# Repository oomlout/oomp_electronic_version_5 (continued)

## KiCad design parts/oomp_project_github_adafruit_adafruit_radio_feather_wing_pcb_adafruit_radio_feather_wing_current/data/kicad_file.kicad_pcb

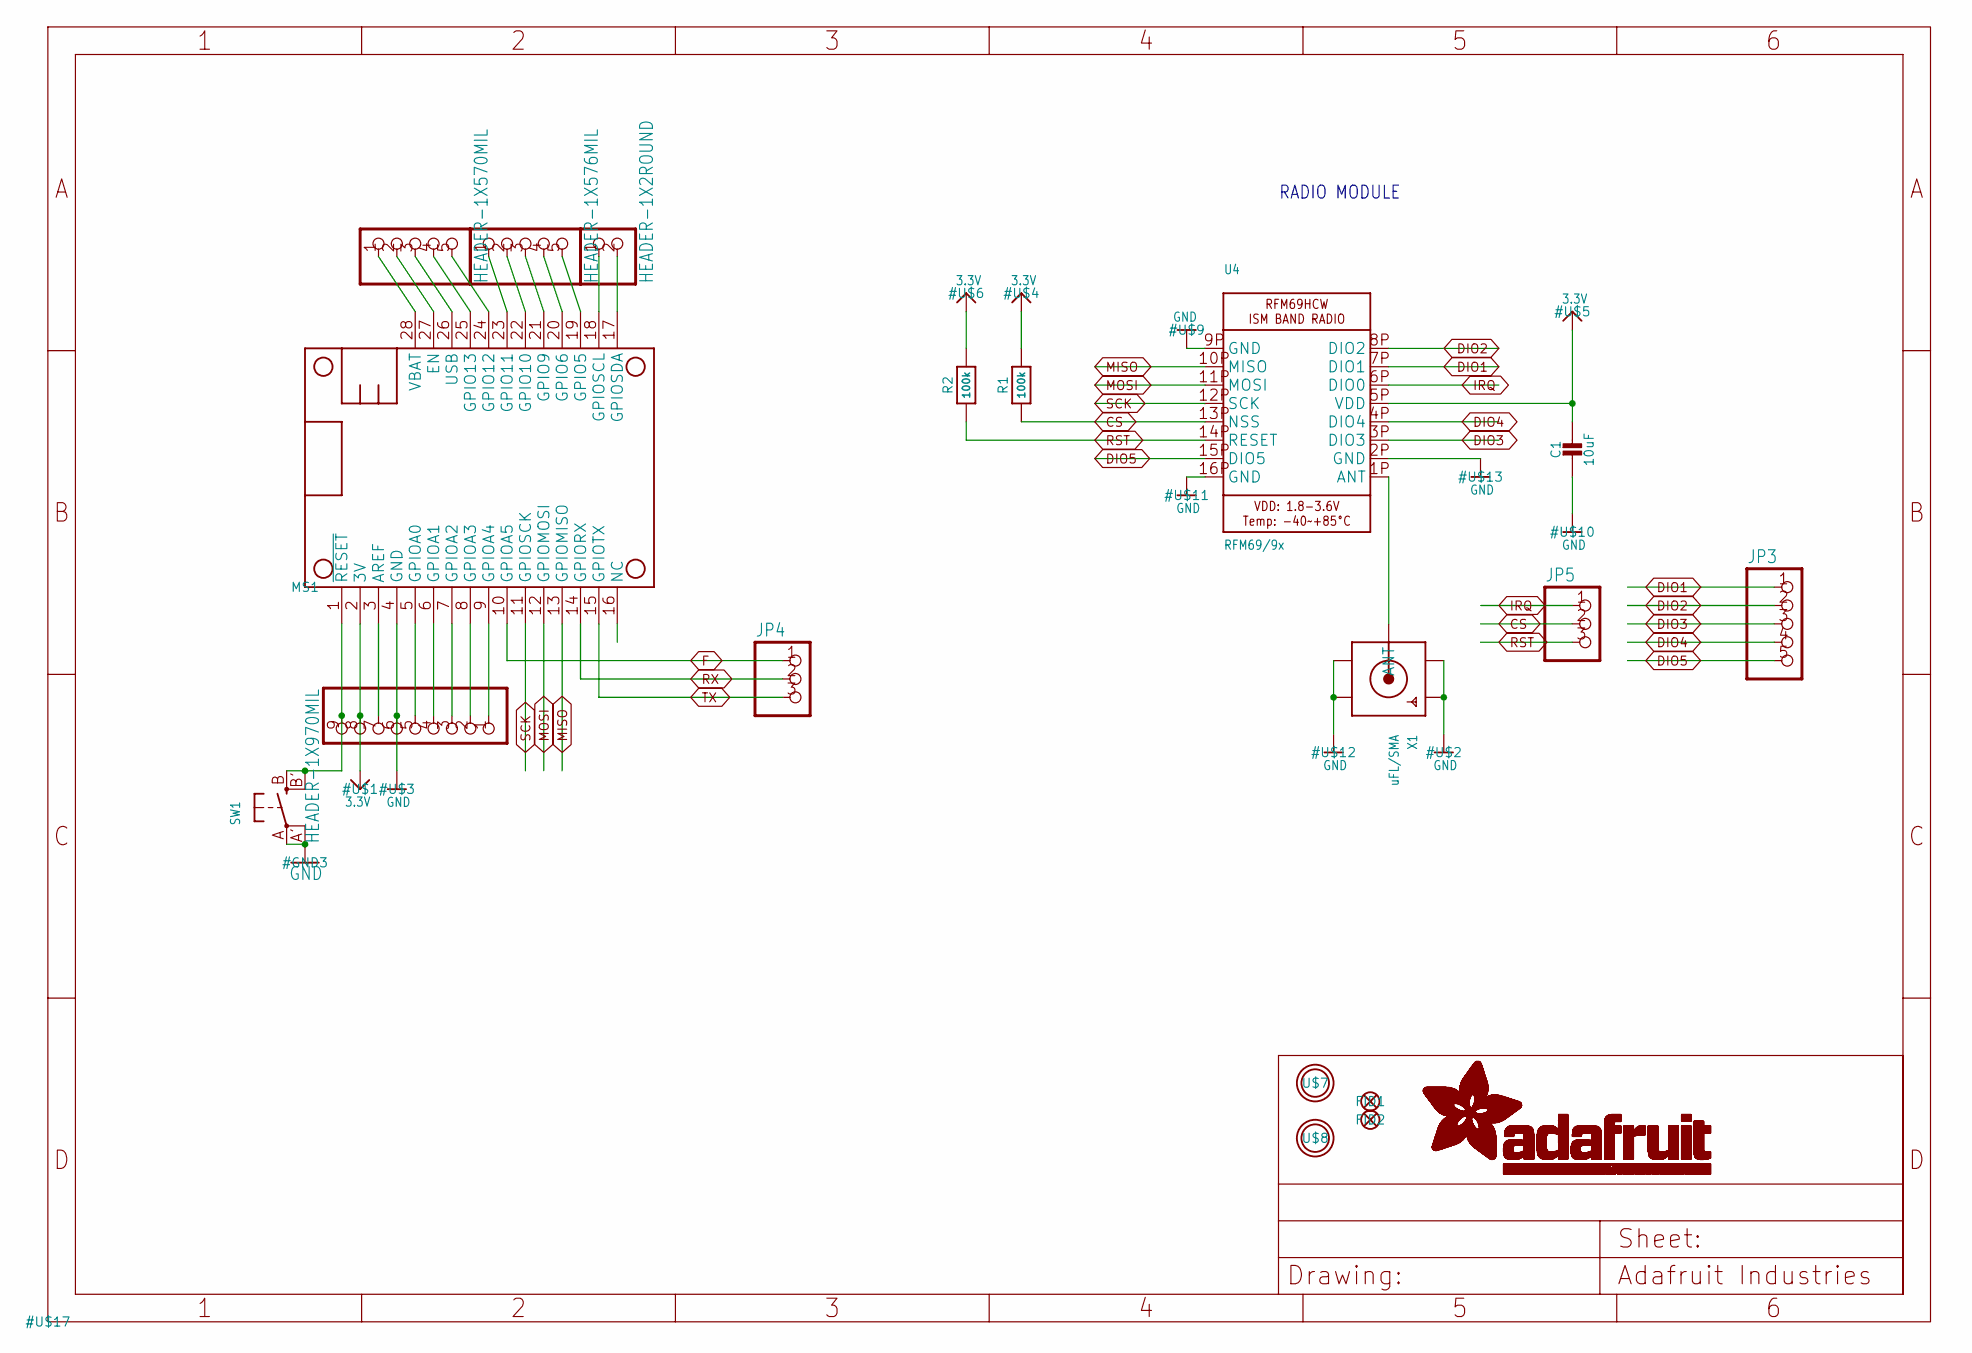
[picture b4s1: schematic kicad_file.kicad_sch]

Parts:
C1: 10uF; 0805-NO
FID1, FID2: FIDUCIAL""; FIDUCIAL_1MM
JP1: HEADER-1X970MIL; 1X09_ROUND_70
JP2, JP3: HEADER-1X570MIL; 1X05_ROUND_70
JP4, JP5: HEADER-1X376MIL; 1X03_ROUND_76
JP6: HEADER-1X2ROUND; 1X02_ROUND
JP7: HEADER-1X576MIL; 1X05_ROUND_76
MS1: FEATHERWING_NOHOLES
R1, R2: 100k; 0603-NO
SW1: SWITCH_TACT_SMT4.6X2.8; BTN_KMR2_4.6X2.8
U4: RFM69/9x; RFMHCW_SMT
U$7, U$8: MOUNTINGHOLE2.5; MOUNTINGHOLE_2.5_PLATED
X1: uFL/SMA; SMA_EDGELAUNCH_UFL

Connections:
3.3V: C1.1, JP1.8, MS1.2 (3V), R1.2, R2.2, U4.5P (VDD)
A: JP7.1, MS1.23 (GPIO11)
ANT: U4.1P (ANT), X1.P (ANT)
B: JP7.2, MS1.22 (GPIO10)
C: JP7.3, MS1.21 (GPIO9)
CS: JP5.2, R1.1, U4.13P (NSS)
D: JP7.4, MS1.20 (GPIO6)
DIO1: JP3.1, U4.7P (DIO1)
DIO2: JP3.2, U4.8P (DIO2)
DIO3: JP3.3, U4.3P (DIO3)
DIO4: JP3.4, U4.4P (DIO4)
DIO5: JP3.5, U4.15P (DIO5)
E: JP7.5, MS1.19 (GPIO5)
EN: JP2.2, MS1.27 (EN)
F: JP4.1, MS1.10 (GPIOA5)
G: JP2.5, MS1.24 (GPIO12)
GND: C1.2, JP1.6, MS1.4 (GND), SW1.A, SW1.A' (P1), U4.2P (GND), U4.9P (GND), U4.16P (GND), X1.GND@1 (GND1), X1.GND@2 (GND2), X1.GND@3 (GND3), X1.GND@4 (GND4)
H: JP2.4, MS1.25 (GPIO13)
I: JP1.5, MS1.5 (GPIOA0)
IRQ: JP5.1, U4.6P (DIO0)
J: JP1.4, MS1.6 (GPIOA1)
K: JP1.3, MS1.7 (GPIOA2)
L: JP1.2, MS1.8 (GPIOA3)
M: JP1.1, MS1.9 (GPIOA4)
MISO: MS1.13 (GPIOMISO), U4.10P (MISO)
MOSI: MS1.12 (GPIOMOSI), U4.11P (MOSI)
unnamed: JP1.7, MS1.3 (AREF)
unnamed: JP1.9, MS1.1 (~RESET), SW1.B (S), SW1.B' (S1)
NC: MS1.16 (NC)
RST: JP5.3, R2.1, U4.14P (RESET)
RX: JP4.2, MS1.14 (GPIORX)
SCK: MS1.11 (GPIOSCK), U4.12P (SCK)
SCL: JP6.1, MS1.18 (GPIOSCL)
SDA: JP6.2, MS1.17 (GPIOSDA)
TX: JP4.3, MS1.15 (GPIOTX)
USB: JP2.3, MS1.26 (USB)
VBAT: JP2.1, MS1.28 (VBAT)

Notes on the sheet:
RADIO MODULE

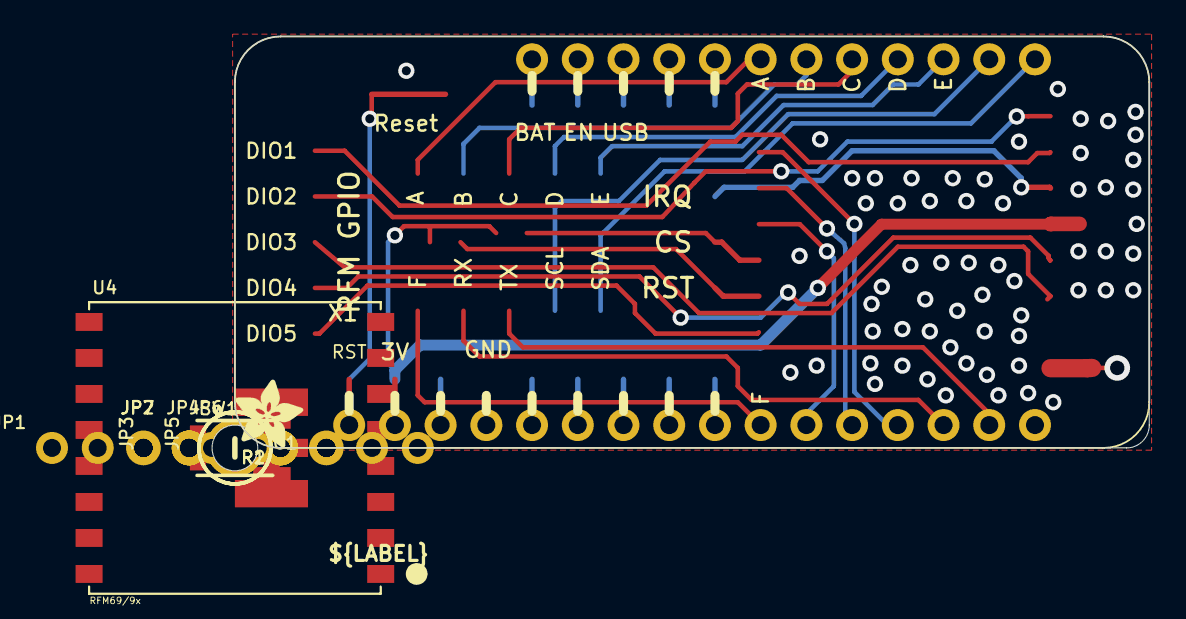
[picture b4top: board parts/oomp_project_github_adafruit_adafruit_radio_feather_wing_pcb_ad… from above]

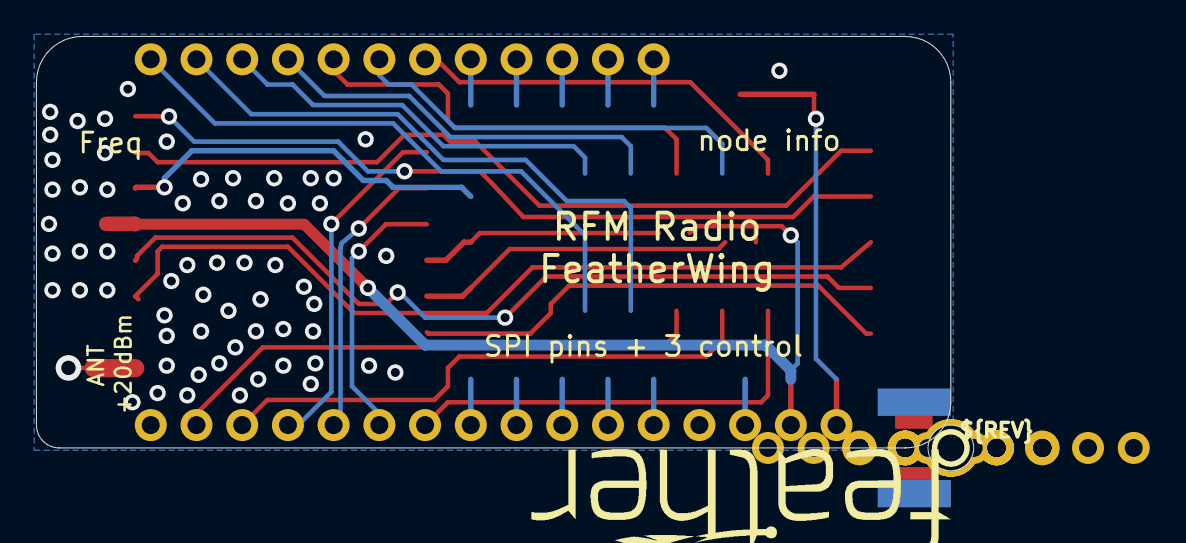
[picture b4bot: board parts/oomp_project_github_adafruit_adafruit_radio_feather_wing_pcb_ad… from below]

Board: 16 copper layers, 50.8 x 22.9 mm, 22 parts (2 on the bottom side), 36 nets.

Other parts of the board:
U$14: PCBFEAT-REV-040
U$15: ADAFRUIT_3.5MM
U$16: FEATHERLOGO
UNK_HOLE_0: dummyfp0

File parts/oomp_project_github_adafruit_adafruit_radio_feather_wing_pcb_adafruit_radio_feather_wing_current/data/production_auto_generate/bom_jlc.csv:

Comment,Designator,Footprint,LCSC Part #
,JP6,Adafruit Radio FeatherWing-import-fps:1X02_ROUND,C492401
,"JP4,JP5",Adafruit Radio FeatherWing-import-fps:1X03_ROUND_76,C49257
,"JP2,JP3",Adafruit Radio FeatherWing-import-fps:1X05_ROUND_70,C42431835
,JP7,Adafruit Radio FeatherWing-import-fps:1X05_ROUND_76,C42431835
,JP1,Adafruit Radio FeatherWing-import-fps:1X09_ROUND_70,C2932701
,U$15,Adafruit Radio FeatherWing-import-fps:ADAFRUIT_3.5MM,
,SW1,Adafruit Radio FeatherWing-import-fps:BTN_KMR2_4.6X2.8,
,U$16,Adafruit Radio FeatherWing-import-fps:FEATHERLOGO,
,U$14,Adafruit Radio FeatherWing-import-fps:PCBFEAT-REV-040,
100k,"R1,R2",Adafruit Radio FeatherWing-import-fps:0603-NO,C25803
10uF,C1,Adafruit Radio FeatherWing-import-fps:0805-NO,
FEATHERWING_NOHOLES,MS1,Adafruit Radio FeatherWing-import-fps:FEATHERWING_NOHOLES,
RFM69/9x,U4,Adafruit Radio FeatherWing-import-fps:RFMHCW_SMT,
uFL/SMA,X1,Adafruit Radio FeatherWing-import-fps:SMA_EDGELAUNCH_UFL,

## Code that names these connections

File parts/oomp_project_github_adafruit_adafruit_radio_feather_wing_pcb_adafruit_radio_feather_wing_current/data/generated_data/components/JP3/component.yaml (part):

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      connected_to:
      - reference: U4
        pin_number: 7P
        pin_name: DIO1
    - number: '2'
      name: '2'
      electrical_type: passive
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      connected_to:
      - reference: U4
        pin_number: 8P
        pin_name: DIO2
    - number: '3'
      name: '3'
      electrical_type: passive
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      connected_to:
      - reference: U4
        pin_number: 3P
        pin_name: DIO3
    - number: '4'
      name: '4'
      electrical_type: passive
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      connected_to:
      - reference: U4
        pin_number: 4P
        pin_name: DIO4
    - number: '5'
      name: '5'
      electrical_type: passive
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      connected_to:
      - reference: U4
        pin_number: 15P
        pin_name: DIO5
    size:
      local_graphics:
        measurement: symbol graphics only; excludes pins, properties, and text
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  connected_components:
  - reference: U4
    pin_number: 15P
    pin_name: DIO5
  - reference: U4
    pin_number: 3P
    pin_name: DIO3
  - reference: U4
    pin_number: 4P
    pin_name: DIO4
  - reference: U4
    pin_number: 7P
    pin_name: DIO1
  - reference: U4
    pin_number: 8P
    pin_name: DIO2
pcb:
  reference: JP3
  value: ''
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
